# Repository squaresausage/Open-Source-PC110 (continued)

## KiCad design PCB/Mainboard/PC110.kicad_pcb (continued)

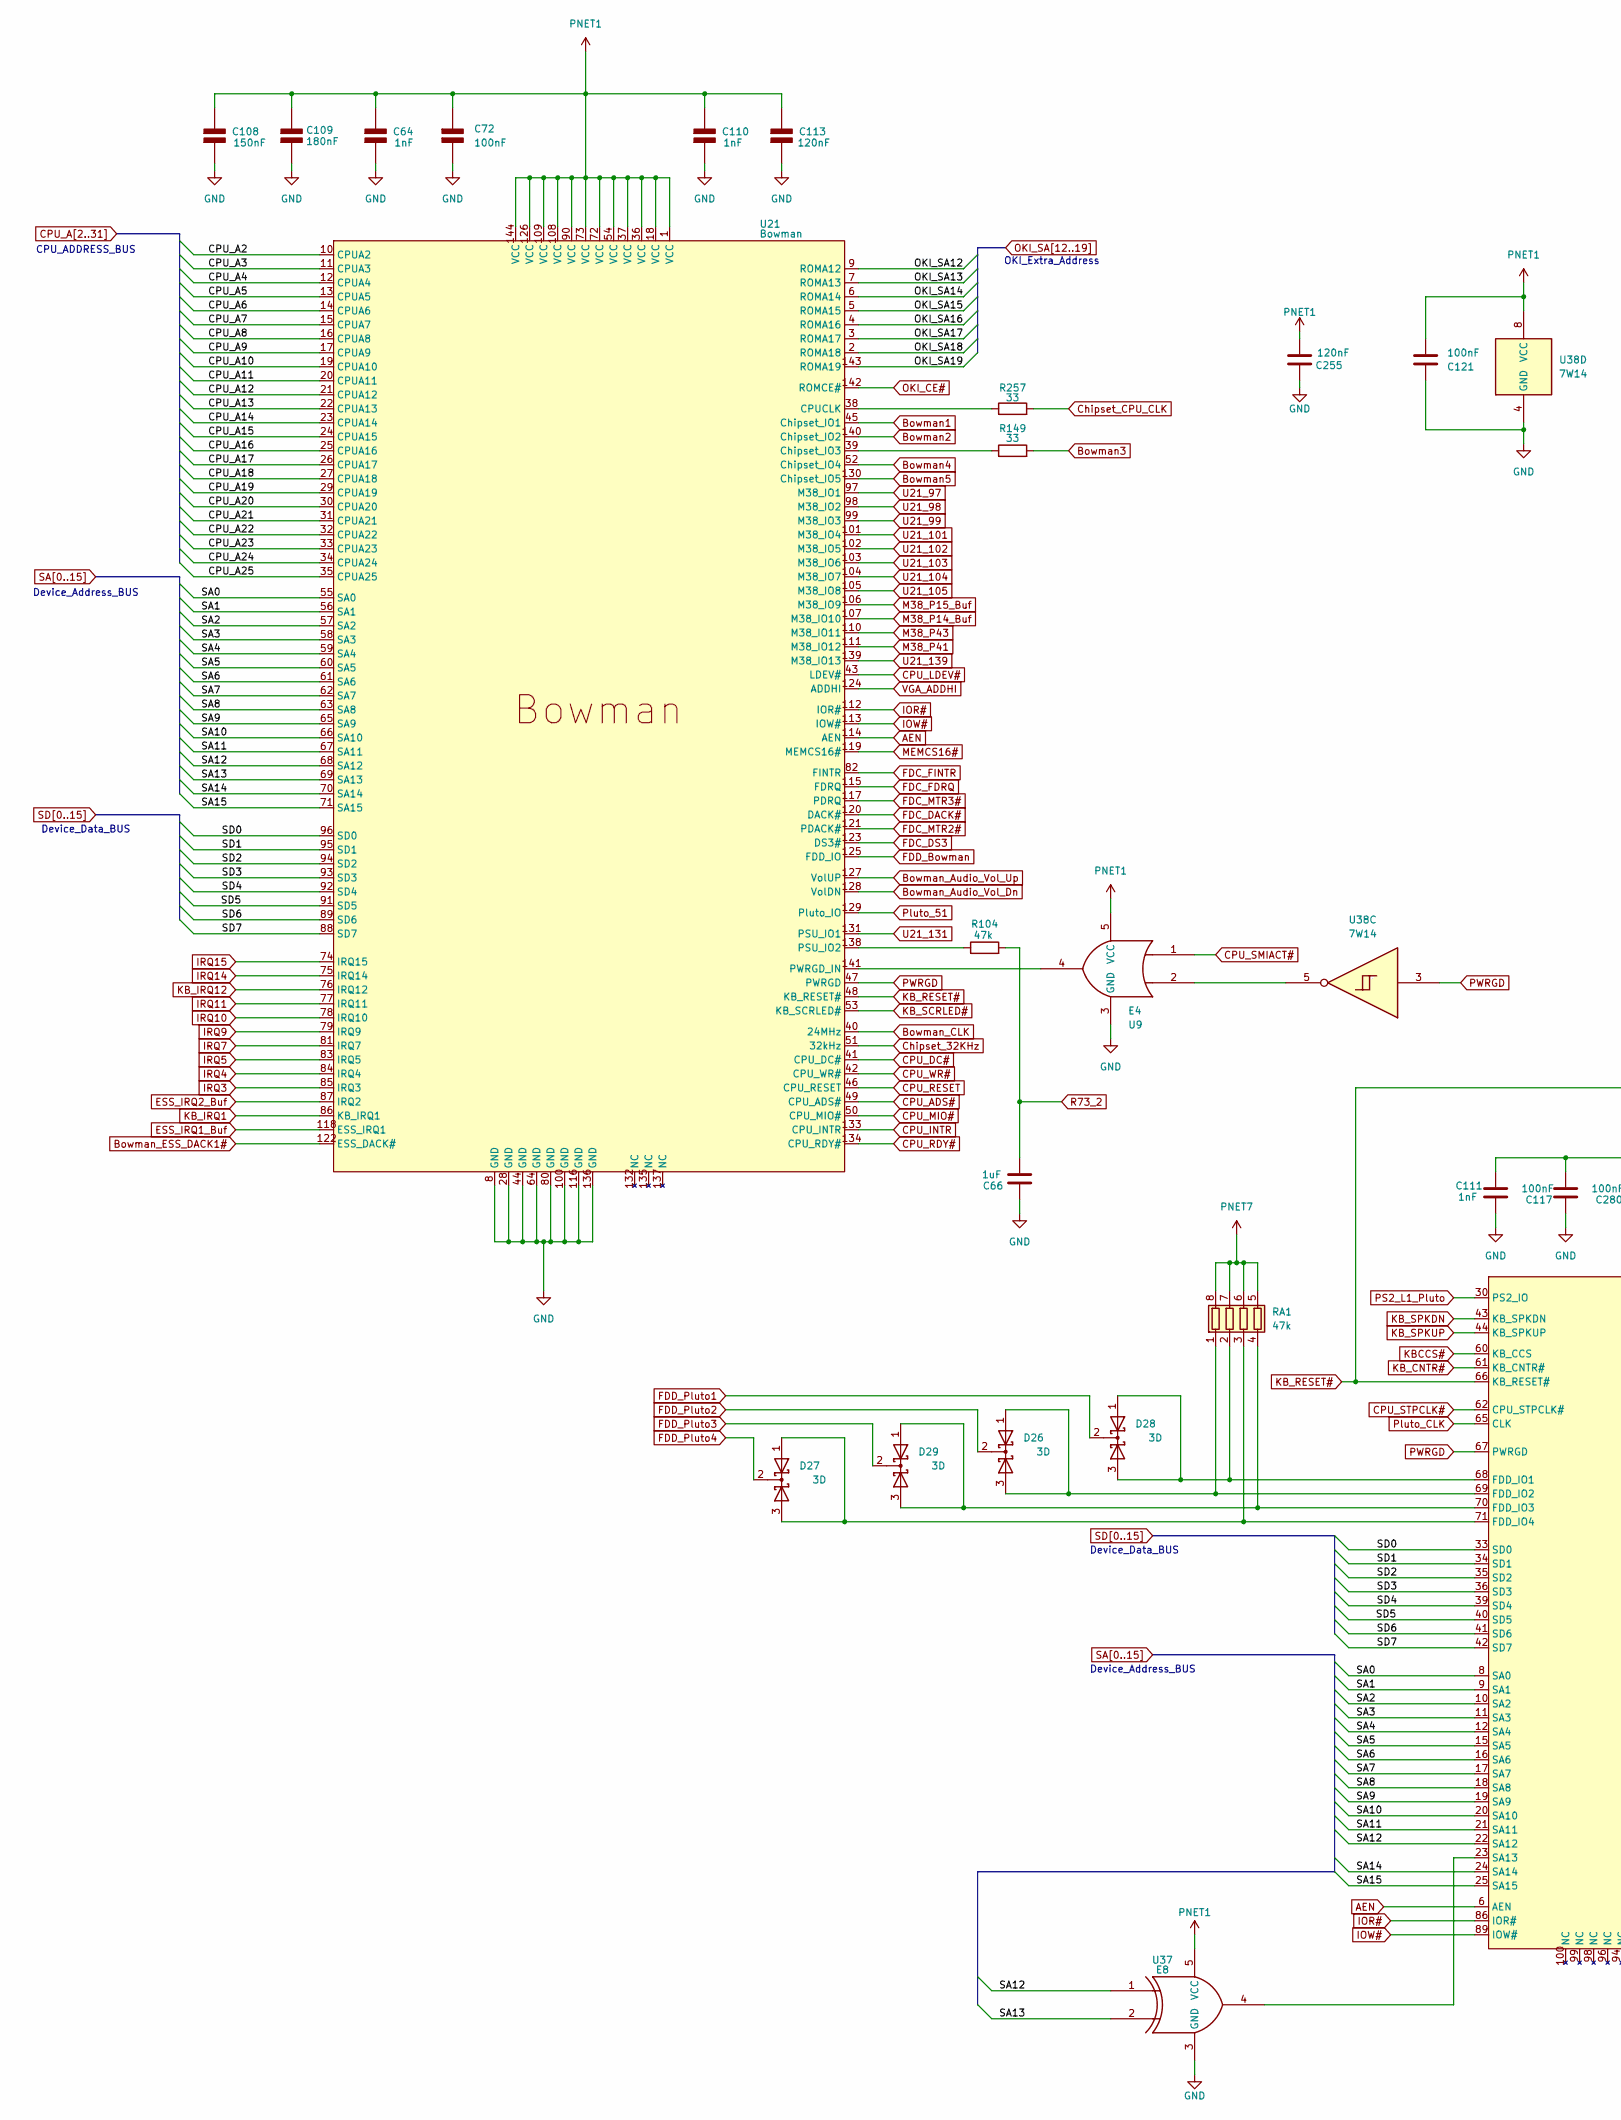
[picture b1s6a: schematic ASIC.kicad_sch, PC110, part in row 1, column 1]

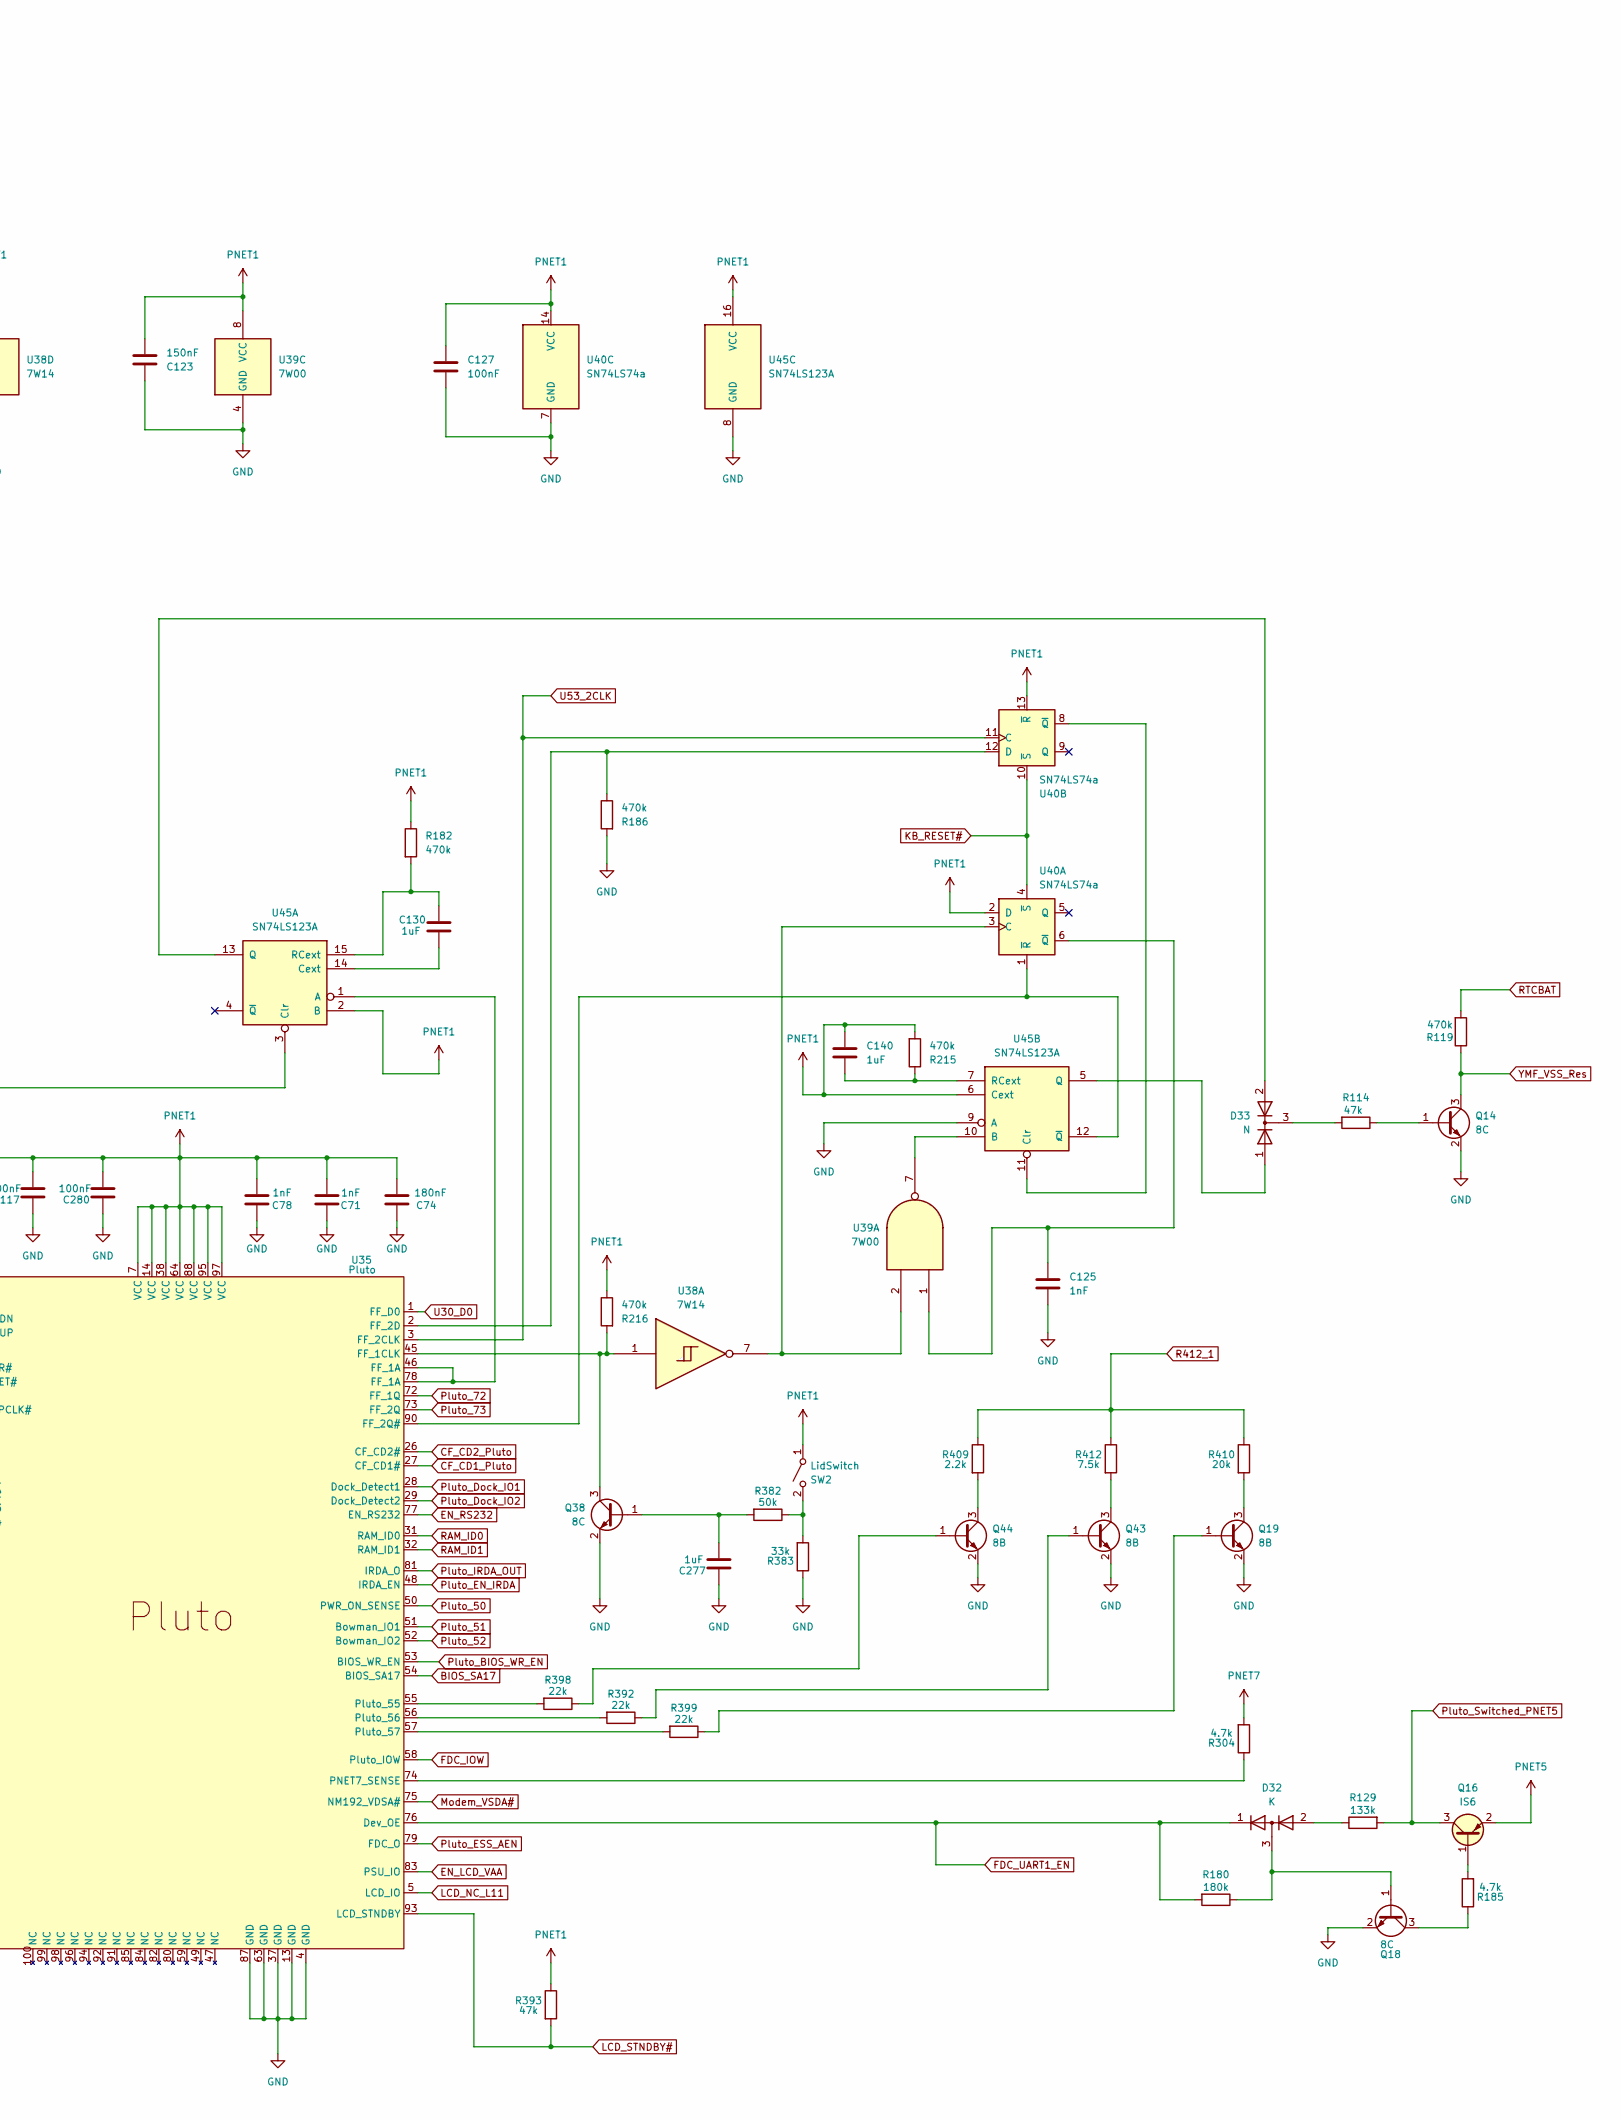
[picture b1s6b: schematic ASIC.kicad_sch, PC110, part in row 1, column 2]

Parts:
C64, C71, C78, C110, C111, C125: 1nF; C_0402_1005Metric
C66, C130, C140, C277: 1uF; C_0603_1608Metric
C72, C117, C121, C127, C280: 100nF; C_0402_1005Metric
C74, C109: 180nF; C_0402_1005Metric
C108, C123: 150nF; C_0402_1005Metric
C113, C255: 120nF; C_0402_1005Metric
D26, D27, D28, D29: 3D
D32: K; SOT-416L
D33: N; SOT-416
Q14, Q18, Q38: 8C; SOT-416
Q16: IS6; TSOT-23
Q19: 8B; SOT-416
Q43, Q44: 8B; SOT-523
R104, R114, R393: 47k; R_0402_1005Metric
R119, R182, R186, R215, R216: 470k; R_0402_1005Metric
R129: 133k; R_0402_1005Metric
R149, R257: 33; R_0402_1005Metric
R180: 180k; R_0402_1005Metric
R185, R304: 4.7k; R_0402_1005Metric
R382: 50k; R_0402_1005Metric
R383: 33k; R_0402_1005Metric
R392, R398, R399: 22k; R_0402_1005Metric
R409: 2.2k; R_0402_1005Metric
R410: 20k; R_0402_1005Metric
R412: 7.5k; R_0402_1005Metric
RA1: 47k; R-array
SW2: LidSwitch
U9: E4; SOT-353
U21: Bowman
U35: Pluto
U37: E8; SOT-353
U38: 7W14; sso-8
U39: 7W00; sso-8
U40: SN74LS74a; TSSOP-14_4.4x5mm_P0.65mm
U45: SN74LS123A; TSSOP-16_4.4x5mm_P0.65mm

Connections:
AEN: U21.114 (AEN), U35.6 (AEN); also elsewhere on the board
BIOS_SA17: U35.54 (BIOS_SA17); also elsewhere on the board
Bowman1: U21.45 (Chipset_IO1); also elsewhere on the board
Bowman2: U21.140 (Chipset_IO2); also elsewhere on the board
Bowman3: R149.2; also elsewhere on the board
Bowman4: U21.52 (Chipset_IO4); also elsewhere on the board
Bowman5: U21.130 (Chipset_IO5); also elsewhere on the board
Bowman_Audio_Vol_Dn: U21.128 (VolDN); also elsewhere on the board
Bowman_Audio_Vol_Up: U21.127 (VolUP); also elsewhere on the board
Bowman_CLK: U21.40 (24MHz); also elsewhere on the board
Bowman_ESS_DACK1#: U21.122 (ESS_DACK#); also elsewhere on the board
CF_CD1_Pluto: U35.27 (CF_CD1#); also elsewhere on the board
CF_CD2_Pluto: U35.26 (CF_CD2#); also elsewhere on the board
CPU_A2: U21.10 (CPUA2); also elsewhere on the board
CPU_A3: U21.11 (CPUA3); also elsewhere on the board
CPU_A4: U21.12 (CPUA4); also elsewhere on the board
CPU_A5: U21.13 (CPUA5); also elsewhere on the board
CPU_A6: U21.14 (CPUA6); also elsewhere on the board
CPU_A7: U21.15 (CPUA7); also elsewhere on the board
CPU_A8: U21.16 (CPUA8); also elsewhere on the board
CPU_A9: U21.17 (CPUA9); also elsewhere on the board
CPU_A10: U21.19 (CPUA10); also elsewhere on the board
CPU_A11: U21.20 (CPUA11); also elsewhere on the board
CPU_A12: U21.21 (CPUA12); also elsewhere on the board
CPU_A13: U21.22 (CPUA13); also elsewhere on the board
CPU_A14: U21.23 (CPUA14); also elsewhere on the board
CPU_A15: U21.24 (CPUA15); also elsewhere on the board
CPU_A16: U21.25 (CPUA16); also elsewhere on the board
CPU_A17: U21.26 (CPUA17); also elsewhere on the board
CPU_A18: U21.27 (CPUA18); also elsewhere on the board
CPU_A19: U21.29 (CPUA19); also elsewhere on the board
CPU_A20: U21.30 (CPUA20); also elsewhere on the board
CPU_A21: U21.31 (CPUA21); also elsewhere on the board
CPU_A22: U21.32 (CPUA22); also elsewhere on the board
CPU_A23: U21.33 (CPUA23); also elsewhere on the board
CPU_A24: U21.34 (CPUA24); also elsewhere on the board
CPU_A25: U21.35 (CPUA25); also elsewhere on the board
CPU_ADS#: U21.49 (CPU_ADS#); also elsewhere on the board
CPU_DC#: U21.41 (CPU_DC#); also elsewhere on the board
CPU_INTR: U21.133 (CPU_INTR); also elsewhere on the board
CPU_LDEV#: U21.43 (LDEV#); also elsewhere on the board
CPU_MIO#: U21.50 (CPU_MIO#); also elsewhere on the board
CPU_RDY#: U21.134 (CPU_RDY#); also elsewhere on the board
CPU_RESET: U21.46 (CPU_RESET); also elsewhere on the board
CPU_SMIACT#: U9.1; also elsewhere on the board
CPU_STPCLK#: U35.62 (CPU_STPCLK#); also elsewhere on the board
CPU_WR#: U21.42 (CPU_WR#); also elsewhere on the board
Chipset_32KHz: U21.51 (32kHz); also elsewhere on the board
Chipset_CPU_CLK: R257.2; also elsewhere on the board
EN_LCD_VAA: U35.83 (PSU_IO); also elsewhere on the board
EN_RS232: U35.77 (EN_RS232); also elsewhere on the board
ESS_IRQ1_Buf: U21.118 (ESS_IRQ1); also elsewhere on the board
ESS_IRQ2_Buf: U21.87 (IRQ2); also elsewhere on the board
FDC_DACK#: U21.120 (DACK#); also elsewhere on the board
FDC_DS3: U21.123 (DS3#); also elsewhere on the board
FDC_FDRQ: U21.115 (FDRQ); also elsewhere on the board
FDC_FINTR: U21.82 (FINTR); also elsewhere on the board
FDC_IOW: U35.58 (Pluto_IOW); also elsewhere on the board
FDC_MTR2#: U21.121 (PDACK#); also elsewhere on the board
FDC_MTR3#: U21.117 (PDRQ); also elsewhere on the board
FDC_UART1_EN: D32.1 (K), R180.2, U35.76 (Dev_OE); also elsewhere on the board
FDD_Bowman: U21.125 (FDD_IO); also elsewhere on the board
FDD_Pluto1: D28.2 (K); also elsewhere on the board
FDD_Pluto2: D26.2 (K); also elsewhere on the board
FDD_Pluto3: D29.2 (K); also elsewhere on the board
FDD_Pluto4: D27.2 (K); also elsewhere on the board
IOR#: U21.112 (IOR#), U35.86 (IOR#); also elsewhere on the board
IOW#: U21.113 (IOW#), U35.89 (IOW#); also elsewhere on the board
IRQ3: U21.85 (IRQ3); also elsewhere on the board
IRQ4: U21.84 (IRQ4); also elsewhere on the board
IRQ5: U21.83 (IRQ5); also elsewhere on the board
IRQ7: U21.81 (IRQ7); also elsewhere on the board
IRQ9: U21.79 (IRQ9); also elsewhere on the board
IRQ10: U21.78 (IRQ10); also elsewhere on the board
IRQ11: U21.77 (IRQ11); also elsewhere on the board
IRQ14: U21.75 (IRQ14); also elsewhere on the board
IRQ15: U21.74 (IRQ15); also elsewhere on the board
KBCCS#: U35.60 (KB_CCS); also elsewhere on the board
KB_CNTR#: U35.61 (KB_CNTR#); also elsewhere on the board
KB_IRQ1: U21.86 (KB_IRQ1); also elsewhere on the board
KB_IRQ12: U21.76 (IRQ12); also elsewhere on the board
KB_RESET#: U21.48 (KB_RESET#), U35.66 (KB_RESET#), U40.4 (~S), U40.10 (~S), U45.3 (Clr); also elsewhere on the board
KB_SCRLED#: U21.53 (KB_SCRLED#); also elsewhere on the board
KB_SPKDN: U35.43 (KB_SPKDN); also elsewhere on the board
KB_SPKUP: U35.44 (KB_SPKUP); also elsewhere on the board
LCD_NC_L11: U35.5 (LCD_IO); also elsewhere on the board
LCD_STNDBY#: R393.2, U35.93 (LCD_STNDBY); also elsewhere on the board
M38_P14_Buf: U21.107 (M38_IO9); also elsewhere on the board
M38_P15_Buf: U21.106 (M38_IO8); also elsewhere on the board
M38_P41: U21.111 (M38_IO11); also elsewhere on the board
M38_P43: U21.110 (M38_IO10); also elsewhere on the board
MEMCS16#: U21.119 (MEMCS16#); also elsewhere on the board
Modem_VSDA#: U35.75 (NM192_VDSA#); also elsewhere on the board
unnamed: D32.2 (A), R129.1
unnamed: D32.3 (common), Q18.1 (B), R180.1
unnamed: D33.3, R114.2
unnamed: Q14.1 (B), R114.1
unnamed: Q16.1 (B), R185.2
unnamed: Q18.3 (C), R185.1
unnamed: Q19.1 (B), R399.1
unnamed: Q19.3 (C), R410.2
unnamed: C277.2, Q38.1 (B), R382.2
unnamed: Q38.3 (C), R216.2, U35.45 (FF_1CLK), U38.1
unnamed: Q43.1 (B), R392.1
unnamed: Q43.3 (C), R412.2
unnamed: Q44.1 (B), R398.1
unnamed: Q44.3 (C), R409.2
unnamed: D26.1 (A), D26.3 (A), RA1.1 (R1.1), U35.69 (FDD_IO2)
unnamed: D28.1 (A), D28.3 (A), RA1.2 (R2.1), U35.68 (FDD_IO1)
unnamed: D27.1 (A), D27.3 (A), RA1.3 (R3.1), U35.71 (FDD_IO4)
unnamed: D29.1 (A), D29.3 (A), RA1.4 (R4.1), U35.70 (FDD_IO3)
unnamed: R257.1, U21.38 (CPUCLK)
unnamed: R149.1, U21.39 (Chipset_IO3)
unnamed: R104.1, U21.138 (PSU_IO2)
unnamed: U9.4, U21.141 (PWRGD_IN)
unnamed: R186.1, U35.2 (FF_2D), U40.12 (D)
unnamed: U35.90 (FF_2Q#), U40.1 (~R), U45.12 (~Q)
unnamed: R304.1, U35.74 (PNET7_SENSE)
unnamed: R398.2, U35.55 (Pluto_55)
unnamed: R392.2, U35.56 (Pluto_56)
unnamed: R399.2, U35.57 (Pluto_57)
unnamed: U35.23 (SA13), U37.4
unnamed: U9.2, U38.5
unnamed: U38.7, U39.2, U40.3 (C)
unnamed: C125.2, U39.1, U40.6 (~Q)
unnamed: U40.8 (~Q), U45.11 (Clr)
unnamed: U35.46 (FF_1A), U35.78 (FF_1A), U45.1 (A)
unnamed: C130.2, U45.14 (Cext)
unnamed: D33.2, U45.13 (Q)
unnamed: C130.1, R182.2, U45.15 (RCext)
unnamed: U39.7, U45.10 (B)
unnamed: D33.1, U45.5 (Q)
unnamed: C140.1, R215.1, U45.7 (RCext)
OKI_CE#: U21.142 (ROMCE#); also elsewhere on the board
OKI_SA12: U21.9 (ROMA12); also elsewhere on the board
OKI_SA13: U21.7 (ROMA13); also elsewhere on the board
OKI_SA14: U21.6 (ROMA14); also elsewhere on the board
OKI_SA15: U21.5 (ROMA15); also elsewhere on the board
OKI_SA16: U21.4 (ROMA16); also elsewhere on the board
OKI_SA17: U21.3 (ROMA17); also elsewhere on the board
OKI_SA18: U21.2 (ROMA18); also elsewhere on the board
OKI_SA19: U21.143 (ROMA19); also elsewhere on the board
PNET1: C64.2 (-), C71.2, C72.1 (+), C74.2, C78.2, C108.2 (-), C109.2 (-), C110.2 (-), C111.1, C113.2 (-), C117.2, C121.1, C123.1, C127.2, C140.2, C255.2, C280.2, R182.1, R215.2, R216.1, R393.1, SW2.1 (A), U9.5 (VCC), U21.1 (VCC), U21.18 (VCC), U21.36 (VCC), U21.37 (VCC), U21.54 (VCC), U21.72 (VCC), U21.73 (VCC), U21.90 (VCC), U21.108 (VCC), U21.109 (VCC), U21.126 (VCC), U21.144 (VCC), U35.7 (VCC), U35.14 (VCC), U35.38 (VCC), U35.64 (VCC), U35.88 (VCC), U35.95 (VCC), U35.97 (VCC), U37.5 (VCC), U38.8 (VCC), U39.8 (VCC), U40.2 (D), U40.13 (~R), U40.14 (VCC), U45.2 (B), U45.6 (Cext), U45.16 (VCC); also elsewhere on the board
PNET7: R304.2, RA1.5 (R4.2), RA1.6 (R3.2), RA1.7 (R2.2), RA1.8 (R1.2); also elsewhere on the board
PS2_L1_Pluto: U35.30 (PS2_IO); also elsewhere on the board
PWRGD: U21.47 (PWRGD), U35.67 (PWRGD), U38.3; also elsewhere on the board
Pluto_50: U35.50 (PWR_ON_SENSE); also elsewhere on the board
Pluto_51: U21.129 (Pluto_IO), U35.51 (Bowman_IO1)
Pluto_52: U35.52 (Bowman_IO2); also elsewhere on the board
Pluto_72: U35.72 (FF_1Q); also elsewhere on the board
Pluto_73: U35.73 (FF_2Q); also elsewhere on the board
Pluto_BIOS_WR_EN: U35.53 (BIOS_WR_EN); also elsewhere on the board
Pluto_CLK: U35.65 (CLK); also elsewhere on the board
Pluto_Dock_IO1: U35.28 (Dock_Detect1); also elsewhere on the board
Pluto_Dock_IO2: U35.29 (Dock_Detect2); also elsewhere on the board
Pluto_EN_IRDA: U35.48 (IRDA_EN); also elsewhere on the board
Pluto_ESS_AEN: U35.79 (FDC_O); also elsewhere on the board
Pluto_IRDA_OUT: U35.81 (IRDA_O); also elsewhere on the board
Pluto_Switched_PNET5: Q16.3 (C), R129.2; also elsewhere on the board
R73_2: C66.2, R104.2; also elsewhere on the board
R412_1: R409.1, R410.1, R412.1; also elsewhere on the board
RTCBAT: R119.2; also elsewhere on the board
SA0: U21.55 (SA0), U35.8 (SA0); also elsewhere on the board
SA1: U21.56 (SA1), U35.9 (SA1); also elsewhere on the board
SA2: U21.57 (SA2), U35.10 (SA2); also elsewhere on the board
SA3: U21.58 (SA3), U35.11 (SA3); also elsewhere on the board
SA4: U21.59 (SA4), U35.12 (SA4); also elsewhere on the board
SA5: U21.60 (SA5), U35.15 (SA5); also elsewhere on the board
SA6: U21.61 (SA6), U35.16 (SA6); also elsewhere on the board
SA7: U21.62 (SA7), U35.17 (SA7); also elsewhere on the board
SA8: U21.63 (SA8), U35.18 (SA8); also elsewhere on the board
SA9: U21.65 (SA9), U35.19 (SA9); also elsewhere on the board
SA10: U21.66 (SA10), U35.20 (SA10); also elsewhere on the board
SA11: U21.67 (SA11), U35.21 (SA11); also elsewhere on the board
SA12: U21.68 (SA12), U35.22 (SA12), U37.1; also elsewhere on the board
SA13: U21.69 (SA13), U37.2; also elsewhere on the board
SA14: U21.70 (SA14), U35.24 (SA14); also elsewhere on the board
SA15: U21.71 (SA15), U35.25 (SA15); also elsewhere on the board
SD0: U21.96 (SD0), U35.33 (SD0); also elsewhere on the board
SD1: U21.95 (SD1), U35.34 (SD1); also elsewhere on the board
SD2: U21.94 (SD2), U35.35 (SD2); also elsewhere on the board
SD3: U21.93 (SD3), U35.36 (SD3); also elsewhere on the board
SD4: U21.92 (SD4), U35.39 (SD4); also elsewhere on the board
SD5: U21.91 (SD5), U35.40 (SD5); also elsewhere on the board
SD6: U21.89 (SD6), U35.41 (SD6); also elsewhere on the board
SD7: U21.88 (SD7), U35.42 (SD7); also elsewhere on the board
SW2-2: R382.1, R383.2, SW2.2 (B)
U21-99: U21.99 (VCC2); also elsewhere on the board
U21_97: U21.97 (M38_IO1); also elsewhere on the board
U21_98: U21.98 (M38_IO2); also elsewhere on the board
U21_101: U21.101 (M38_IO3); also elsewhere on the board
U21_102: U21.102 (M38_IO4); also elsewhere on the board
U21_103: U21.103 (M38_IO5); also elsewhere on the board
U21_104: U21.104 (M38_IO6); also elsewhere on the board
U21_105: U21.105 (M38_IO7); also elsewhere on the board
U21_131: U21.131 (PSU_IO1); also elsewhere on the board
U21_139: U21.139 (M38_IO12); also elsewhere on the board
U30_D0: U35.1 (FF_D0); also elsewhere on the board
U53_2CLK: U35.3 (FF_2CLK), U40.11 (C); also elsewhere on the board
VGA_ADDHI: U21.124 (ADDHI); also elsewhere on the board
YMF_VSS_Res: Q14.3 (C), R119.1; also elsewhere on the board

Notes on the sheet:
OKI_Extra_Address
CPU_ADDRESS_BUS
Device_Data_BUS
Device_Address_BUS

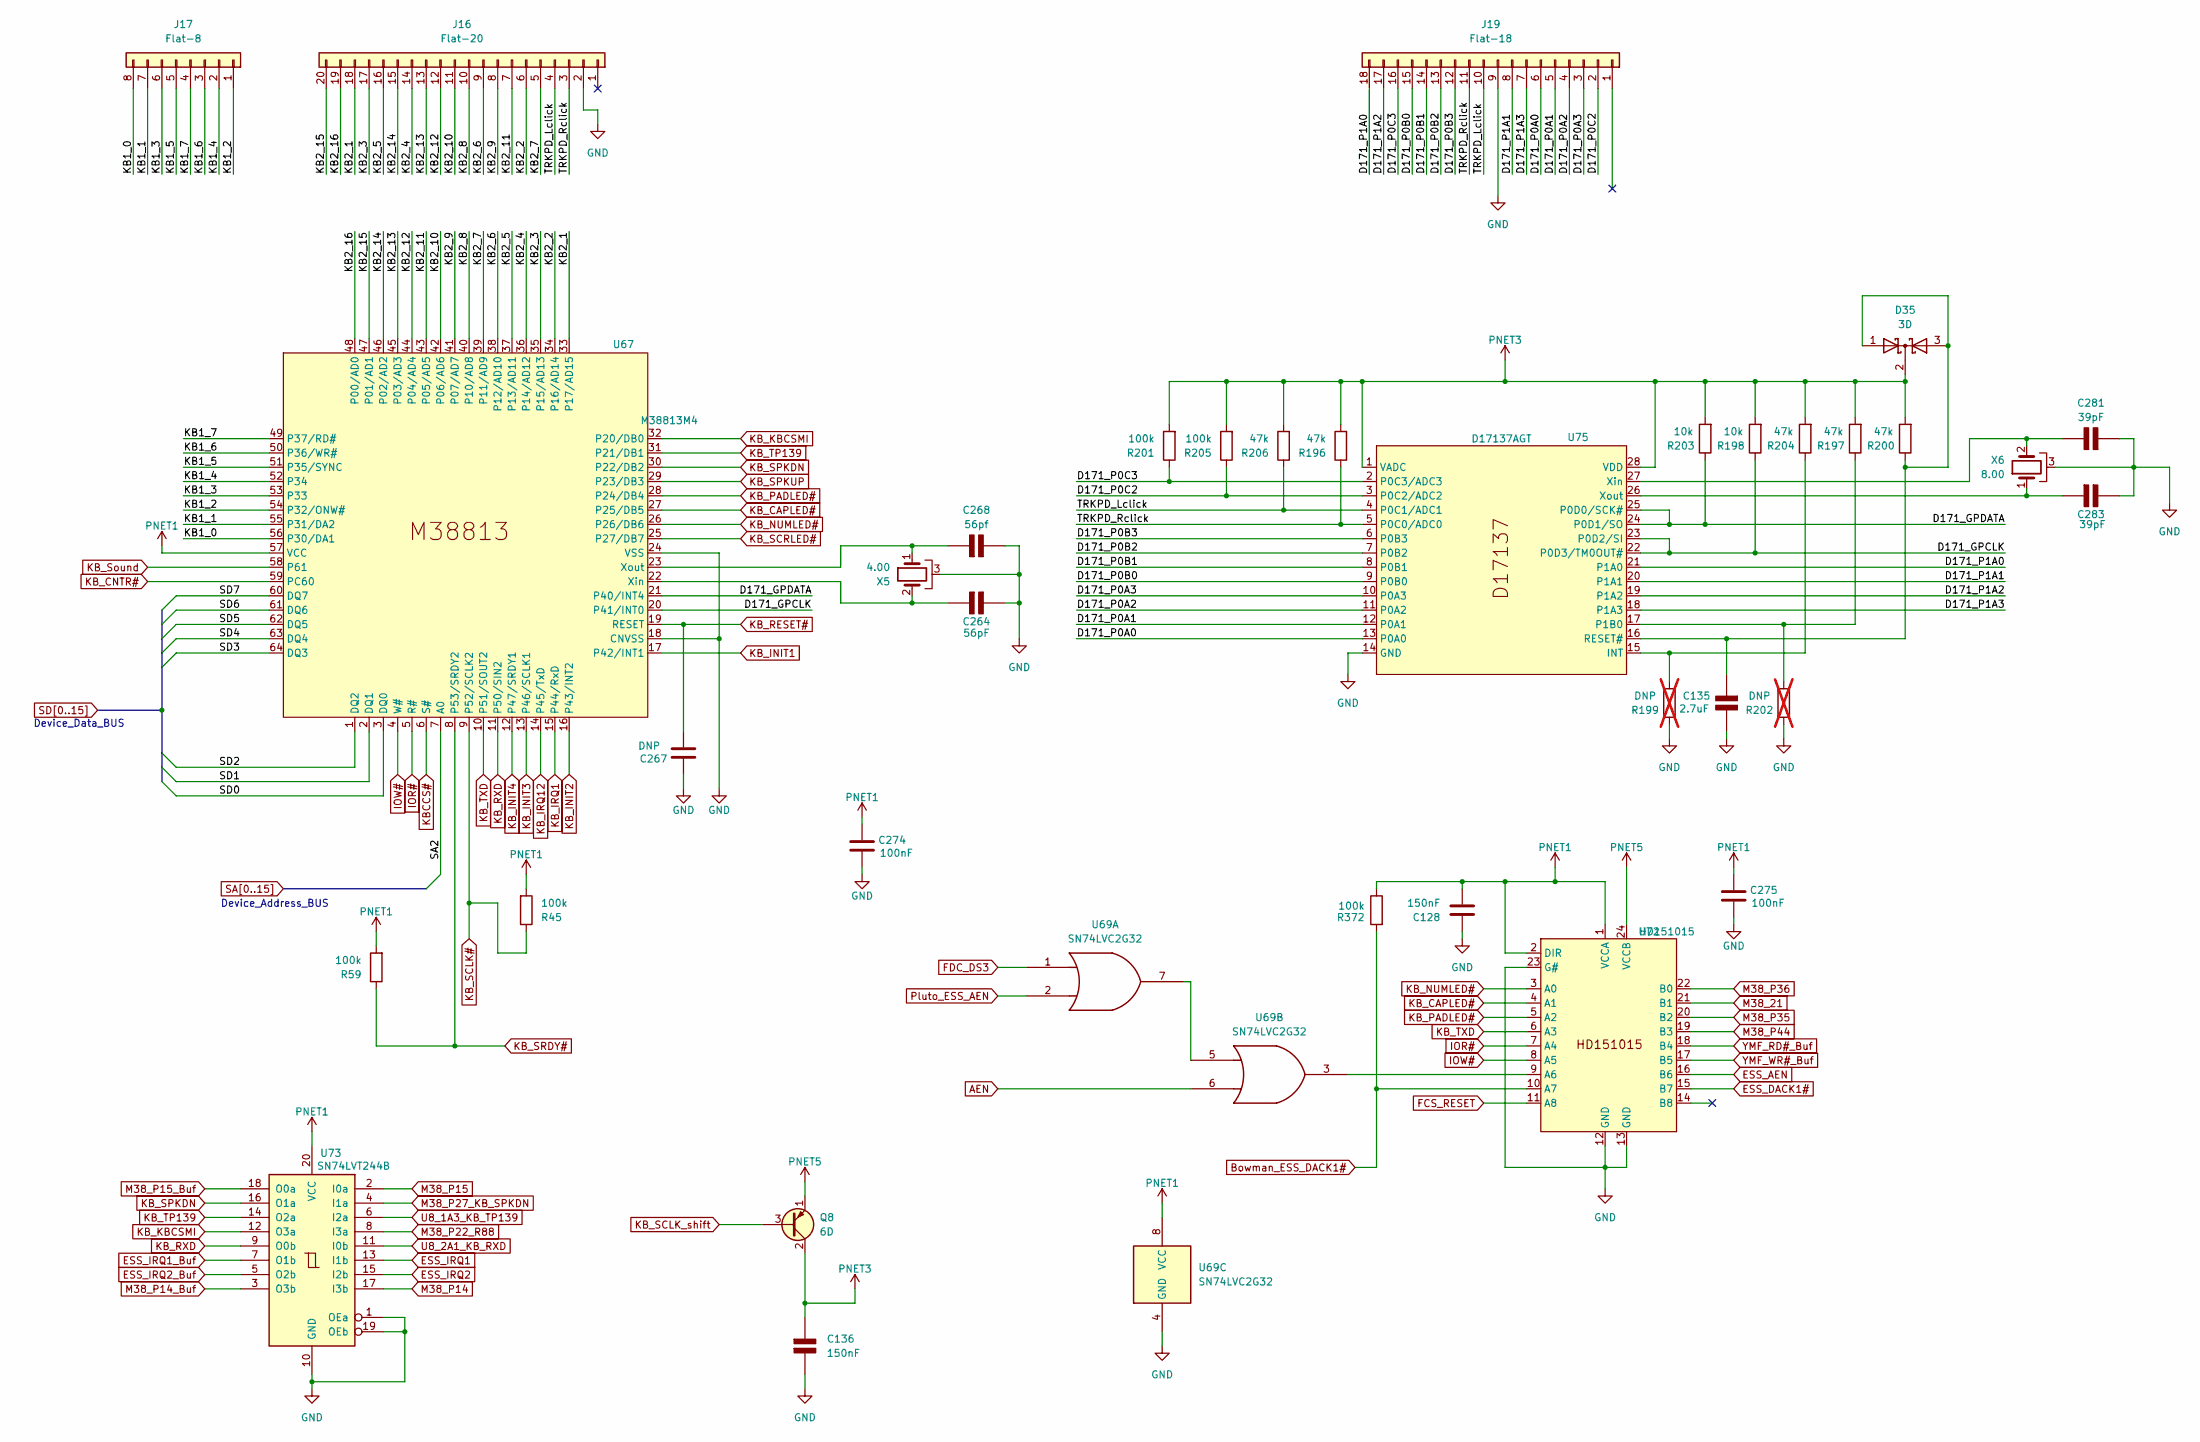
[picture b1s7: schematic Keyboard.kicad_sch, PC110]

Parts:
C128, C136: 150nF; C_0402_1005Metric
C135: 2.7uF; C_0805_2012Metric
C264: 56pF; C_0402_1005Metric
C267: DNP; C_0402_1005Metric
C268: 56pf; C_0402_1005Metric
C274, C275: 100nF; C_0402_1005Metric
C281, C283: 39pF; C_0402_1005Metric
D35: 3D
J16: Flat-20
J17: Flat-8
J19: Flat-18
Q8: 6D; 3D
R45, R59, R201, R205, R372: 100k; R_0402_1005Metric
R196, R197, R200, R204, R206: 47k; R_0402_1005Metric
R198, R203: 10k; R_0402_1005Metric
R199, R202: DNP; R_0402_1005Metric; not fitted
U67: M38813M4; QFN64
U69: SN74LVC2G32; SSOP-8_2.95x2.8mm_P0.65mm
U72: HD151015; SSOP-24_5.3x8.2mm_P0.65mm
U73: SN74LVT244B; TSSOP-20_4.4x6.5mm_P0.65mm
U75: D17137AGT; SSOP-28
X5: 4.00; XTAL-5
X6: 8.00; XTAL-4

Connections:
/Keyboard and Trackpoint/D171_GPCLK: R198.1, U67.20 (P41/INT0), U75.22 (P0D3/TM0OUT#), U75.23 (P0D2/SI)
/Keyboard and Trackpoint/D171_GPDATA: R203.1, U67.21 (P40/INT4), U75.24 (P0D1/SO), U75.25 (P0D0/SCK#)
/Keyboard and Trackpoint/D171_P0A0: J19.6, U75.13 (P0A0)
/Keyboard and Trackpoint/D171_P0A1: J19.5, U75.12 (P0A1)
/Keyboard and Trackpoint/D171_P0A2: J19.4, U75.11 (P0A2)
/Keyboard and Trackpoint/D171_P0A3: J19.3, U75.10 (P0A3)
/Keyboard and Trackpoint/D171_P0B0: J19.15, U75.9 (P0B0)
/Keyboard and Trackpoint/D171_P0B1: J19.14, U75.8 (P0B1)
/Keyboard and Trackpoint/D171_P0B2: J19.13, U75.7 (P0B2)
/Keyboard and Trackpoint/D171_P0B3: J19.12, U75.6 (P0B3)
/Keyboard and Trackpoint/D171_P0C2: J19.2, R205.1, U75.3 (P0C2/ADC2)
/Keyboard and Trackpoint/D171_P0C3: J19.16, R201.1, U75.2 (P0C3/ADC3)
/Keyboard and Trackpoint/D171_P1A0: J19.18, U75.21 (P1A0)
/Keyboard and Trackpoint/D171_P1A1: J19.8, U75.20 (P1A1)
/Keyboard and Trackpoint/D171_P1A2: J19.17, U75.19 (P1A2)
/Keyboard and Trackpoint/D171_P1A3: J19.7, U75.18 (P1A3)
/Keyboard and Trackpoint/KB1_0: J17.8, U67.56 (P30/DA1)
/Keyboard and Trackpoint/KB1_1: J17.7, U67.55 (P31/DA2)
/Keyboard and Trackpoint/KB1_2: J17.1, U67.54 (P32/ONW#)
/Keyboard and Trackpoint/KB1_3: J17.6, U67.53 (P33)
/Keyboard and Trackpoint/KB1_4: J17.2, U67.52 (P34)
/Keyboard and Trackpoint/KB1_5: J17.5, U67.51 (P35/SYNC)
/Keyboard and Trackpoint/KB1_6: J17.3, U67.50 (P36/WR#)
/Keyboard and Trackpoint/KB1_7: J17.4, U67.49 (P37/RD#)
/Keyboard and Trackpoint/KB2_1: J16.18, U67.33 (P17/AD15)
/Keyboard and Trackpoint/KB2_2: J16.6, U67.34 (P16/AD14)
/Keyboard and Trackpoint/KB2_3: J16.17, U67.35 (P15/AD13)
/Keyboard and Trackpoint/KB2_4: J16.14, U67.36 (P14/AD12)
/Keyboard and Trackpoint/KB2_5: J16.16, U67.37 (P13/AD11)
/Keyboard and Trackpoint/KB2_6: J16.9, U67.38 (P12/AD10)
/Keyboard and Trackpoint/KB2_7: J16.5, U67.39 (P11/AD9)
/Keyboard and Trackpoint/KB2_8: J16.10, U67.40 (P10/AD8)
/Keyboard and Trackpoint/KB2_9: J16.8, U67.41 (P07/AD7)
/Keyboard and Trackpoint/KB2_10: J16.11, U67.42 (P06/AD6)
/Keyboard and Trackpoint/KB2_11: J16.7, U67.43 (P05/AD5)
/Keyboard and Trackpoint/KB2_12: J16.12, U67.44 (P04/AD4)
/Keyboard and Trackpoint/KB2_13: J16.13, U67.45 (P03/AD3)
/Keyboard and Trackpoint/KB2_14: J16.15, U67.46 (P02/AD2)
/Keyboard and Trackpoint/KB2_15: J16.20, U67.47 (P01/AD1)
/Keyboard and Trackpoint/KB2_16: J16.19, U67.48 (P00/AD0)
/Keyboard and Trackpoint/TRKPD_Lclick: J16.4, J19.10, R206.1, U75.4 (P0C1/ADC1)
/Keyboard and Trackpoint/TRKPD_Rclick: J16.3, J19.11, R196.1, U75.5 (P0C0/ADC0)
AEN: U69.6; also elsewhere on the board
Bowman_ESS_DACK1#: R372.2, U72.10 (A7); also elsewhere on the board
ESS_AEN: U72.16 (B6); also elsewhere on the board
ESS_DACK1#: U72.15 (B7); also elsewhere on the board
ESS_IRQ1: U73.13 (I1b); also elsewhere on the board
ESS_IRQ1_Buf: U73.7 (O1b); also elsewhere on the board
ESS_IRQ2: U73.15 (I2b); also elsewhere on the board
ESS_IRQ2_Buf: U73.5 (O2b); also elsewhere on the board
FCS_RESET: U72.11 (A8); also elsewhere on the board
FDC_DS3: U69.1; also elsewhere on the board
IOR#: U67.5 (R#), U72.7 (A4); also elsewhere on the board
IOW#: U67.4 (W#), U72.8 (A5); also elsewhere on the board
KBCCS#: U67.6 (S#); also elsewhere on the board
KB_CAPLED#: U67.27 (P25/DB5), U72.4 (A1)
KB_CNTR#: U67.59 (PC60); also elsewhere on the board
KB_INIT1: U67.17 (P42/INT1); also elsewhere on the board
KB_INIT2: U67.16 (P43/INT2); also elsewhere on the board
KB_INIT3: U67.13 (P46/SCLK1); also elsewhere on the board
KB_INIT4: U67.12 (P47/SRDY1); also elsewhere on the board
KB_IRQ1: U67.15 (P44/RxD); also elsewhere on the board
KB_IRQ12: U67.14 (P45/TxD); also elsewhere on the board
KB_KBCSMI: U67.32 (P20/DB0), U73.12 (O3a)
KB_NUMLED#: U67.26 (P26/DB6), U72.3 (A0)
KB_PADLED#: U67.28 (P24/DB4), U72.5 (A2)
KB_RESET#: C267.2, U67.19 (RESET); also elsewhere on the board
KB_RXD: U67.11 (P50/SIN2), U73.9 (O0b)
KB_SCLK#: R45.1, U67.9 (P52/SCLK2); also elsewhere on the board
KB_SCLK_shift: Q8.3 (B); also elsewhere on the board
KB_SCRLED#: U67.25 (P27/DB7); also elsewhere on the board
KB_SPKDN: U67.30 (P22/DB2), U73.16 (O1a); also elsewhere on the board
KB_SPKUP: U67.29 (P23/DB3); also elsewhere on the board
KB_SRDY#: R59.1, U67.8 (P53/SRDY2); also elsewhere on the board
KB_Sound: U67.58 (P61); also elsewhere on the board
KB_TP139: U67.31 (P21/DB1), U73.14 (O2a)
KB_TXD: U67.10 (P51/SOUT2), U72.6 (A3)
M38_21: U72.21 (B1); also elsewhere on the board
M38_P14: U73.17 (I3b); also elsewhere on the board
M38_P14_Buf: U73.3 (O3b); also elsewhere on the board
M38_P15: U73.2 (I0a); also elsewhere on the board
M38_P15_Buf: U73.18 (O0a); also elsewhere on the board
M38_P22_R88: U73.8 (I3a); also elsewhere on the board
M38_P27_KB_SPKDN: U73.4 (I1a); also elsewhere on the board
M38_P35: U72.20 (B2); also elsewhere on the board
M38_P36: U72.22 (B0); also elsewhere on the board
M38_P44: U72.19 (B3); also elsewhere on the board
unnamed: C135.1 (+), D35.1 (A), D35.3 (A), R200.1, U75.16 (RESET#)
unnamed: C264.2 (-), U67.22 (Xin), X5.2
unnamed: C268.2 (-), U67.23 (Xout), X5.1
unnamed: U69.5, U69.7
unnamed: U69.3, U72.9 (A6)
unnamed: R199.2, R204.1, U75.15 (INT)
unnamed: R197.1, R202.2, U75.17 (P1B0)
PNET1: C128.1, C274.1, C275.1, R45.2, R59.2, R372.1, U67.57 (VCC), U69.8 (VCC), U72.1 (VCCA), U72.2 (DIR), U73.20 (VCC); also elsewhere on the board
PNET3: C136.1 (+), D35.2 (K), Q8.2 (C), R196.2, R197.2, R198.2, R200.2, R201.2, R203.2, R204.2, R205.2, R206.2, U75.1 (VADC), U75.28 (VDD)
Pluto_ESS_AEN: U69.2; also elsewhere on the board
SA2: U67.7 (A0); also elsewhere on the board
SD0: U67.3 (DQ0); also elsewhere on the board
SD1: U67.2 (DQ1); also elsewhere on the board
SD2: U67.1 (DQ2); also elsewhere on the board
SD3: U67.64 (DQ3); also elsewhere on the board
SD4: U67.63 (DQ4); also elsewhere on the board
SD5: U67.62 (DQ5); also elsewhere on the board
SD6: U67.61 (DQ6); also elsewhere on the board
SD7: U67.60 (DQ7); also elsewhere on the board
U8_1A3_KB_TP139: U73.6 (I2a); also elsewhere on the board
U8_2A1_KB_RXD: U73.11 (I0b); also elsewhere on the board
YMF_RD#_Buf: U72.18 (B4); also elsewhere on the board
YMF_WR#_Buf: U72.17 (B5); also elsewhere on the board

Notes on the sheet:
Device_Address_BUS
Device_Data_BUS
